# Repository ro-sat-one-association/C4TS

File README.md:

# C4TS
https://www.facebook.com/c4tsinspace/

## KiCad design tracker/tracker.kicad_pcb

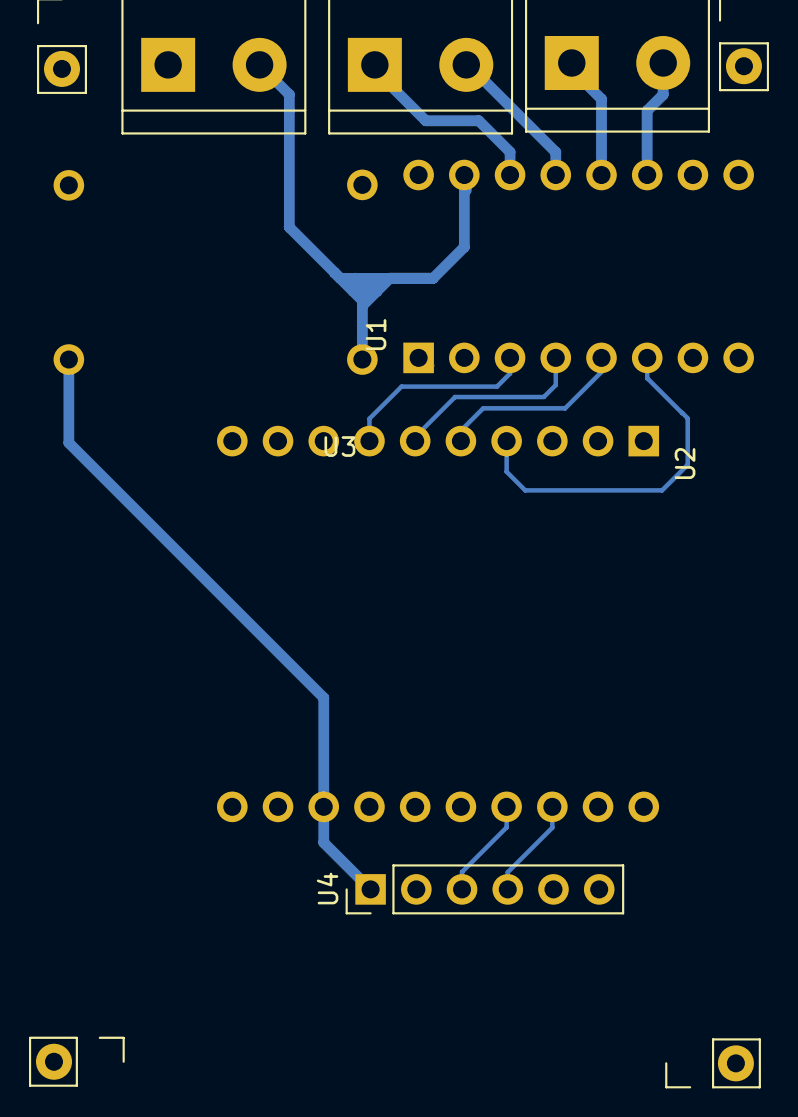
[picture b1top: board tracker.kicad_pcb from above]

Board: 2 copper layers, 7 parts (0 on the bottom side), 13 nets.

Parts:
J1: Conn_01x02; TerminalBlock_bornier-2_P5.08mm
M1: Motor_DC -A-; TerminalBlock_bornier-2_P5.08mm
M2: Motor_DC2 -B-; TerminalBlock_bornier-2_P5.08mm
U1: DRV8833
U2: ESP8266(3.3); ESP8266
U3: pwr_reg
U4: M10DOF; Pin_Header_Straight_1x06_Pitch2.54mm

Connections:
+3V3: U2.19, U3.4, U4.1
+BATT: J1.2, U1.15, U3.1
GND: J1.1, U1.16, U2.10, U2.17, U2.18, U3.2, U3.3, U4.2
unnamed: M1.1, U1.12
unnamed: M1.2, U1.11
unnamed: M2.1, U1.14
unnamed: M2.2, U1.13
unnamed: U1.3, U2.7
unnamed: U1.4, U2.6
unnamed: U1.5, U2.5
unnamed: U1.6, U2.4
unnamed: U2.23, U4.3
unnamed: U2.24, U4.4

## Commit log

2017-11-03 RPi -> Arduino Pro Mini Driver -> APRS Radio
2017-11-03 Added "<APRS>" flag to the text sent by the RPi
2017-11-05 Basic driver changes
2017-12-19 cripturi de camera:{
2018-01-28 Monitorizare baterie + Driver radio
2018-02-03 Driver functional
2018-03-05 Procedura de verificare a senzorilor la pornire + APRS
2018-03-05 + Camera check
2018-03-06 Weather report format script
2018-03-12 SHT21
2018-03-26 Tracker + Cod Busola MPU + SoftwareSerial Rx/Tx script
2018-03-26 gitignore
2018-04-24 GPS functional, HW balon complet! (SPER)
2018-04-27 pseudobiblioteca pentru GSM
2018-04-29 Separat colectarea de trimitere, testat cazurile de eroare, TODO: vezi cum stabilesti starea camerei
2018-05-04 Inceput de cod final
2018-05-06 Aproape gata
2018-05-08 Unelte interfata sol
2018-05-14 start.sh modificat
2018-05-15 Procesare mai buna pentru sol din aprs.fi
2018-05-16 PyCurl pentru APRS.fi, urllib2 pentru localhost
2018-05-19 Am adaugat trackerul
2018-05-26 MPU + Card separat
2018-05-28 Add files via upload
    Schema ProMini-Card-M10DOF
2018-06-02 Adaugat modulu' lu Pascues .zip
2018-06-02 SMS instant la reintrarea in altitudine
2018-06-05 Rezolvat GSM
2018-06-08 Primire de date direct de pe serverele aprs, inceput
2018-06-11 APRS -> Habhub
2018-06-11 main.py = upload_habitat + interfata locala
2018-06-11 Am scos monolitul
2018-06-14 Putina curatenie
2018-06-18 Adaugat logo
2018-06-18 Modificari la procesarea de sol, parola suplimentara
2018-06-18 script alternativ pentru luat datele de pe .fi + script adaugare toate datele
2018-07-01 temperatura externa = SHT, nu BMP in pana mea
2018-07-12 Curatenie si aliniere antena
2018-09-22 Date si scheme
2018-11-15 Sters două fișiere ce nu aveau ce căuta în /Final
2018-11-23 Incercare documentatie (in lucru)
2019-03-16 Mare documentatie adaugata
